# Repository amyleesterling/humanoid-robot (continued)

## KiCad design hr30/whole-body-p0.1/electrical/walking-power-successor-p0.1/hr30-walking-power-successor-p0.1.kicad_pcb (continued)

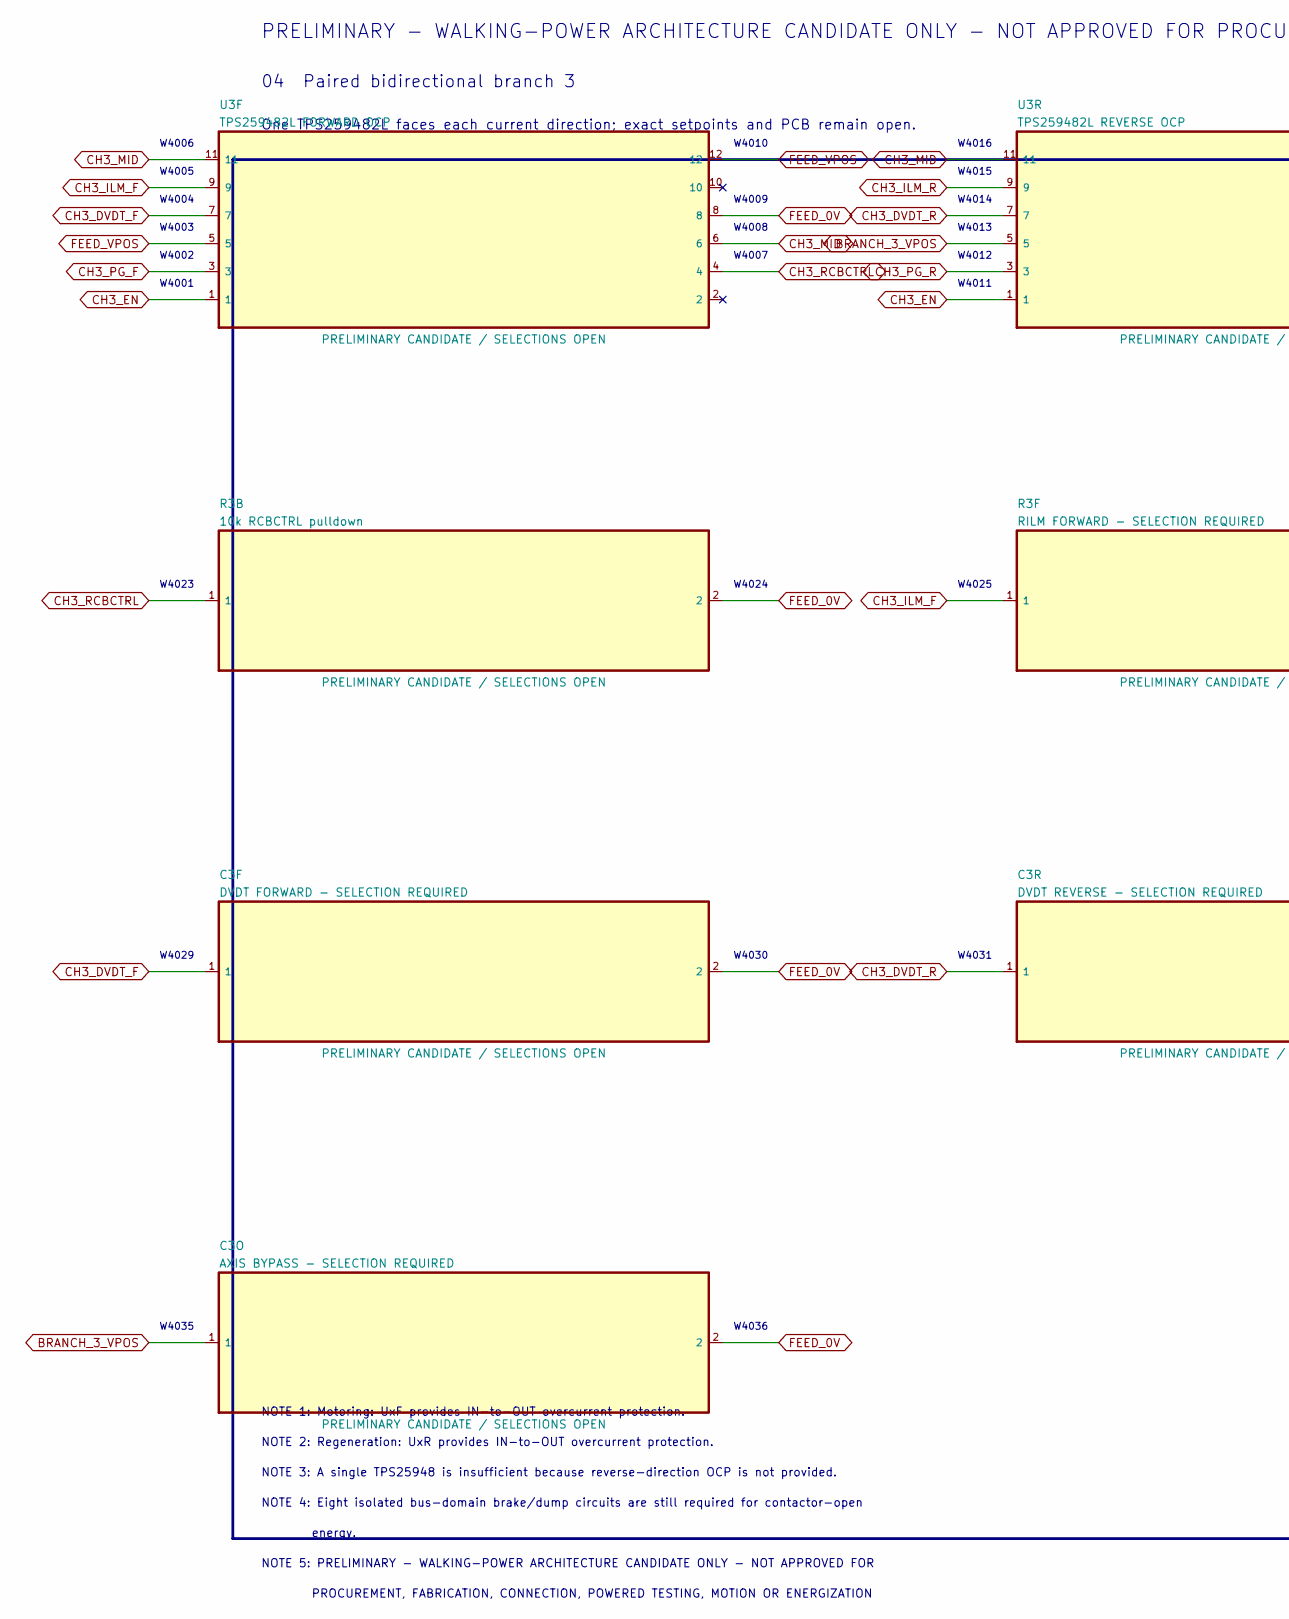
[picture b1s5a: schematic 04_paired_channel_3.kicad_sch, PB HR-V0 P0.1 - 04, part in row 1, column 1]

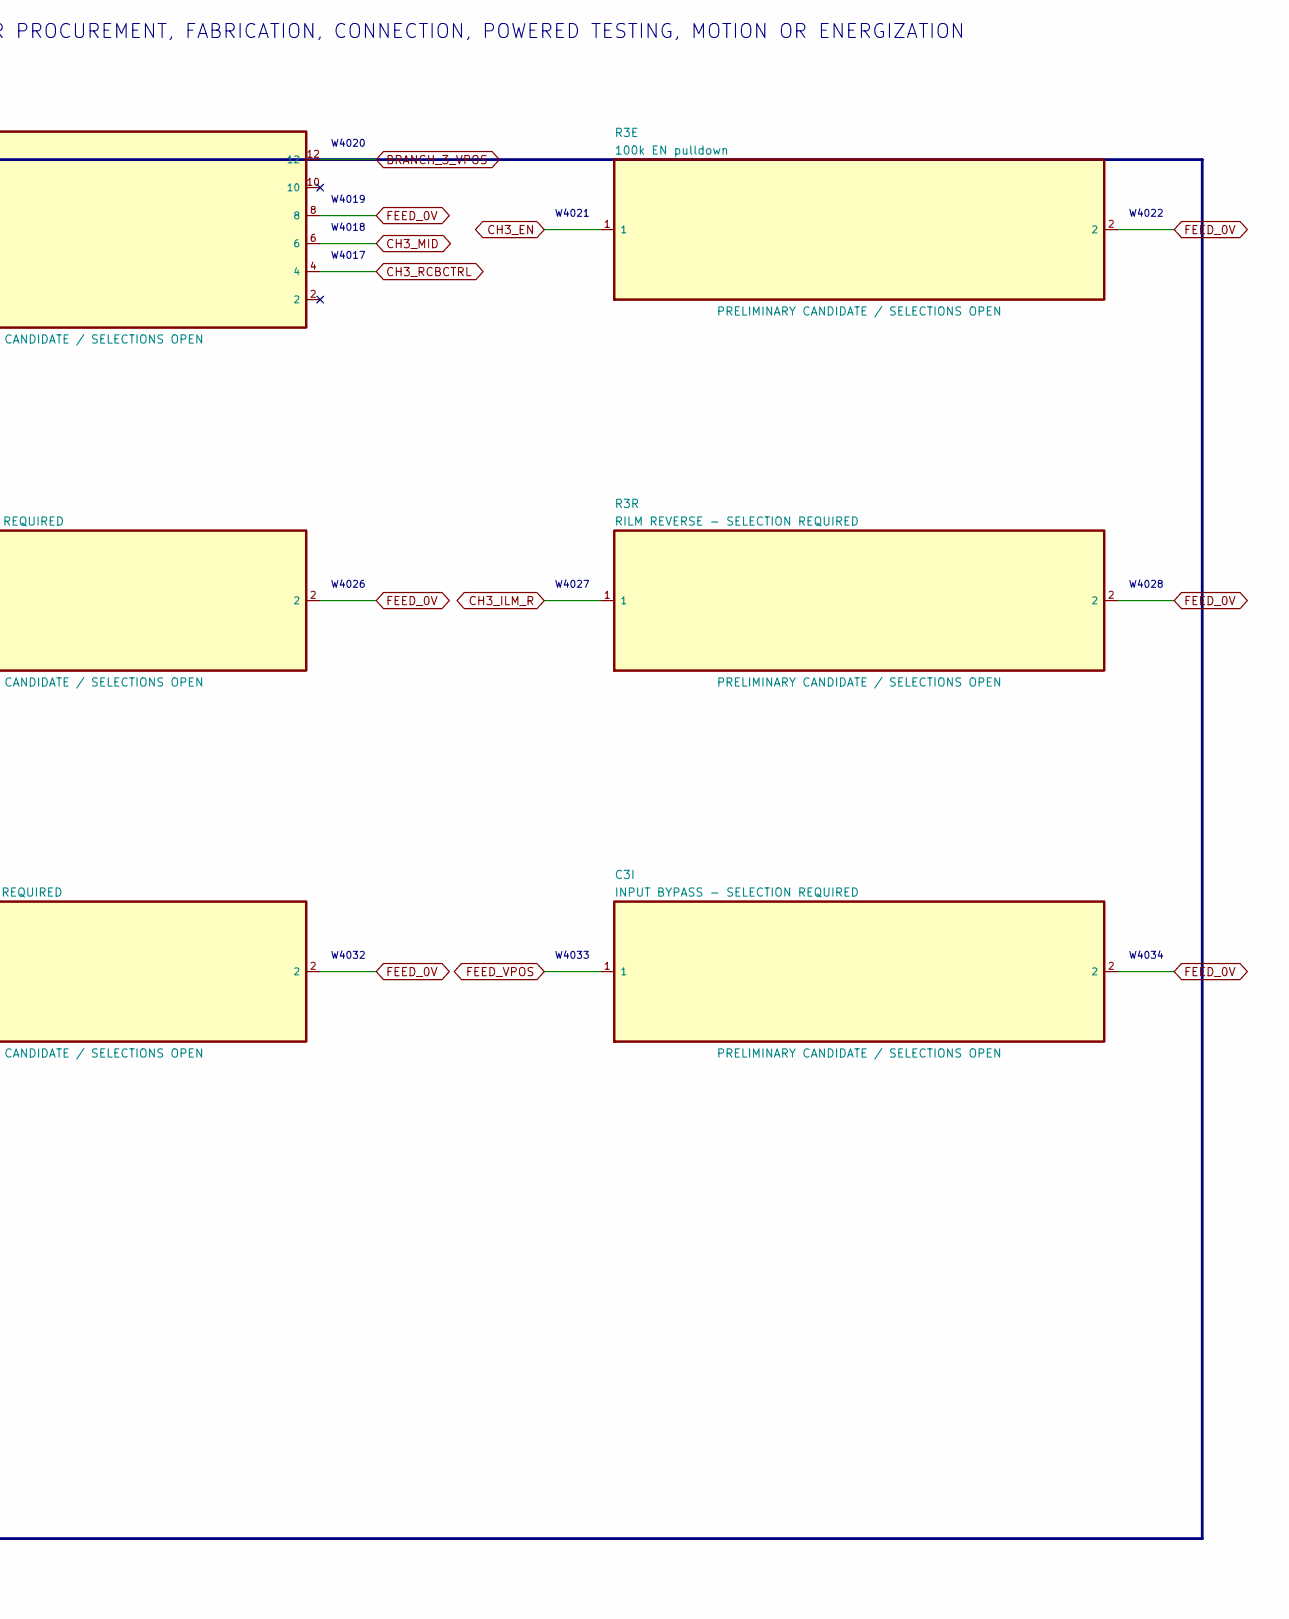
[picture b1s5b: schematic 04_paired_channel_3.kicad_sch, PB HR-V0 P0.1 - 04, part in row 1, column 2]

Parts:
C3F: DVDT FORWARD - SELECTION REQUIRED; C_0603_1608Metric
C3I: INPUT BYPASS - SELECTION REQUIRED; C_0805_2012Metric
C3O: AXIS BYPASS - SELECTION REQUIRED; C_0805_2012Metric
C3R: DVDT REVERSE - SELECTION REQUIRED; C_0603_1608Metric
R3B: 10k RCBCTRL pulldown; R_0603_1608Metric
R3E: 100k EN pulldown; R_0603_1608Metric
R3F: RILM FORWARD - SELECTION REQUIRED; R_0603_1608Metric
R3R: RILM REVERSE - SELECTION REQUIRED; R_0603_1608Metric
U3F: TPS259482L FORWARD OCP
U3R: TPS259482L REVERSE OCP

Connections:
BRANCH_3_VPOS: C3O.1, U3R.5, U3R.12; also elsewhere on the board
CH3_DVDT_F: C3F.1, U3F.7
CH3_DVDT_R: C3R.1, U3R.7
CH3_EN: R3E.1, U3F.1, U3R.1; also elsewhere on the board
CH3_ILM_F: R3F.1, U3F.9; also elsewhere on the board
CH3_ILM_R: R3R.1, U3R.9; also elsewhere on the board
CH3_ITIMER_F: U3F.10
CH3_ITIMER_R: U3R.10
CH3_MID: U3F.6, U3F.11, U3R.6, U3R.11
CH3_OV_F: U3F.2; also elsewhere on the board
CH3_OV_R: U3R.2; also elsewhere on the board
CH3_PG_F: U3F.3; also elsewhere on the board
CH3_PG_R: U3R.3; also elsewhere on the board
CH3_RCBCTRL: R3B.1, U3F.4, U3R.4; also elsewhere on the board
FEED_0V: C3F.2, C3I.2, C3O.2, C3R.2, R3B.2, R3E.2, R3F.2, R3R.2, U3F.8, U3R.8; also elsewhere on the board
FEED_VPOS: C3I.1, U3F.5, U3F.12; also elsewhere on the board

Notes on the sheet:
PRELIMINARY - WALKING-POWER ARCHITECTURE CANDIDATE ONLY - NOT APPROVED FOR PROCUREMENT, FABRICATION, CONNECTION, POWERED TESTING, MOTION OR ENERGIZATION
04 Paired bidirectional branch 3
One TPS259482L faces each current direction; exact setpoints and PCB remain open.
W4001
W4002
W4003
W4004
W4005
W4006
W4007
W4008
W4009
W4010
W4011
W4012
W4013
W4014
W4015
W4016
W4017
W4018
W4019
W4020
W4021
W4022
W4023
W4024
W4025
W4026
W4027
W4028
W4029
W4030
W4031
W4032
W4033
W4034
W4035
W4036
NOTE 1: Motoring: UxF provides IN-to-OUT overcurrent protection.

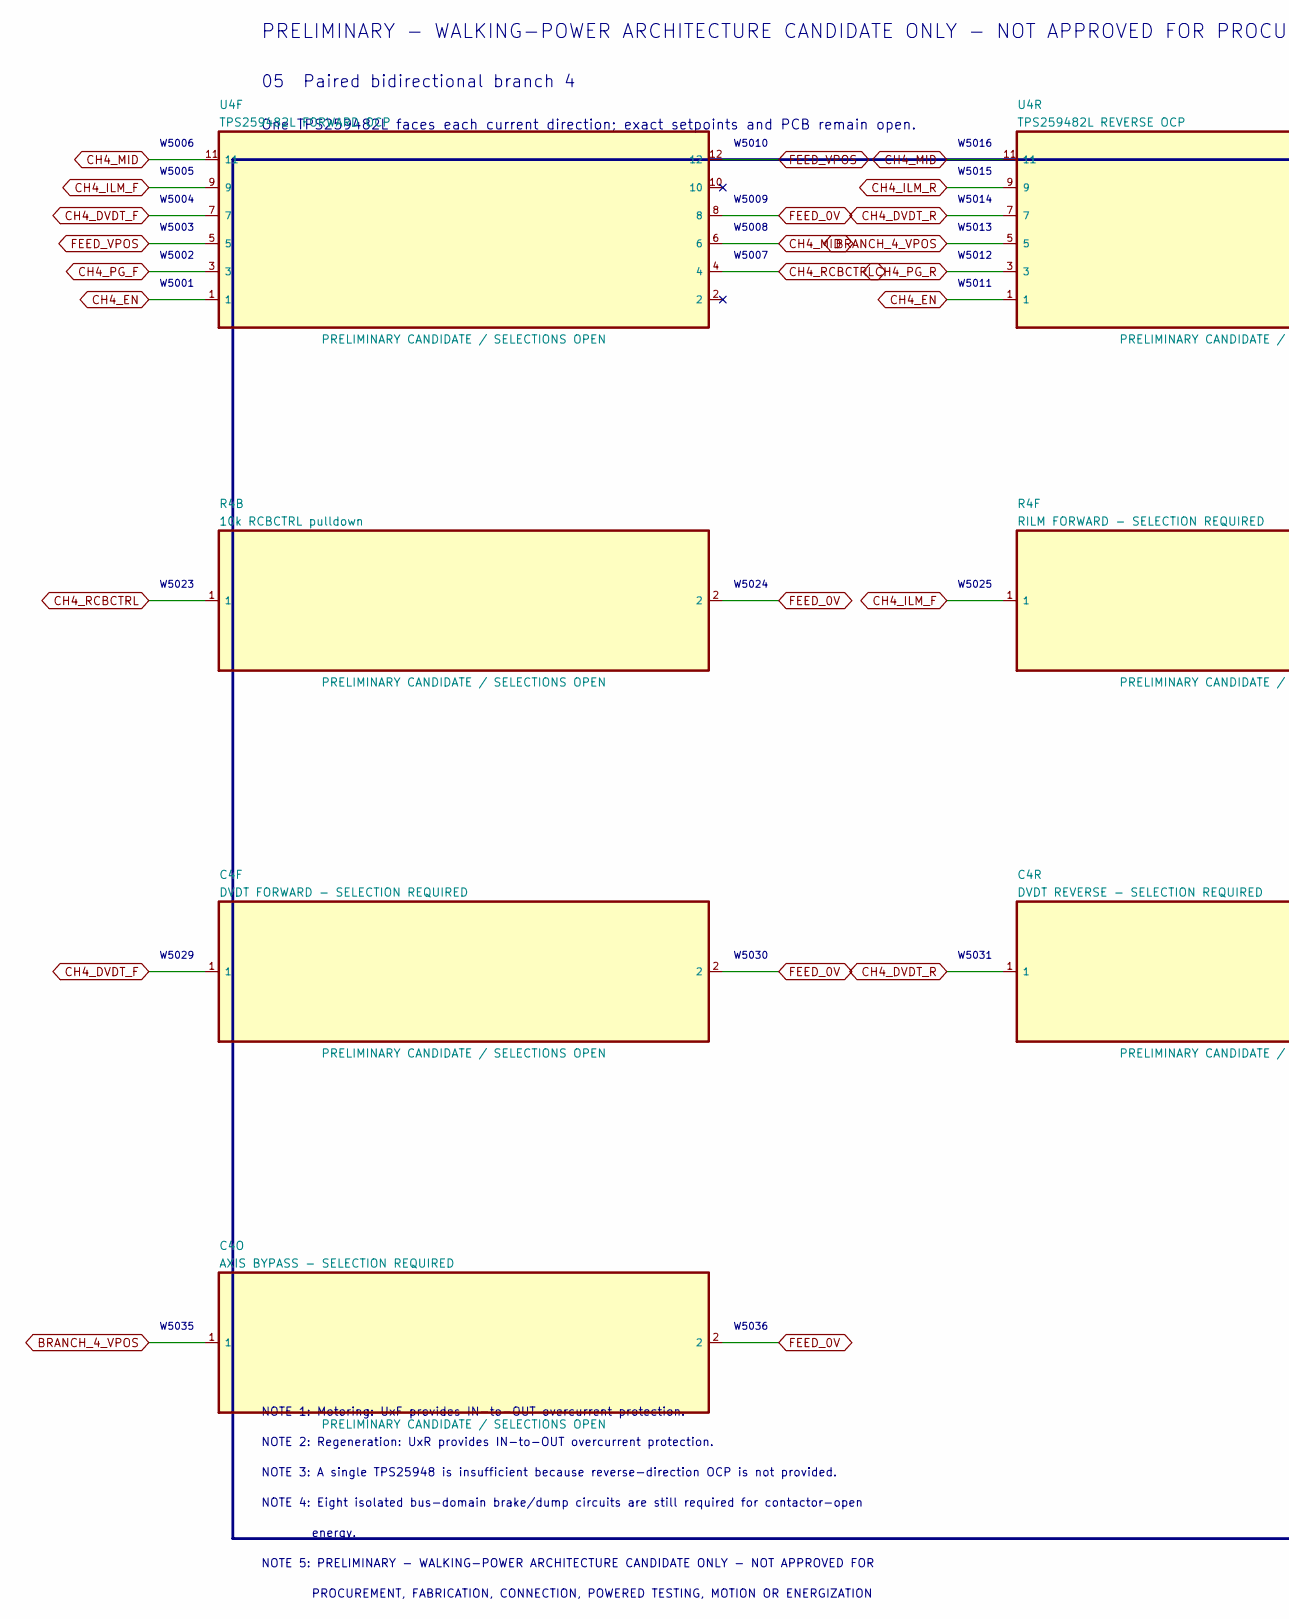
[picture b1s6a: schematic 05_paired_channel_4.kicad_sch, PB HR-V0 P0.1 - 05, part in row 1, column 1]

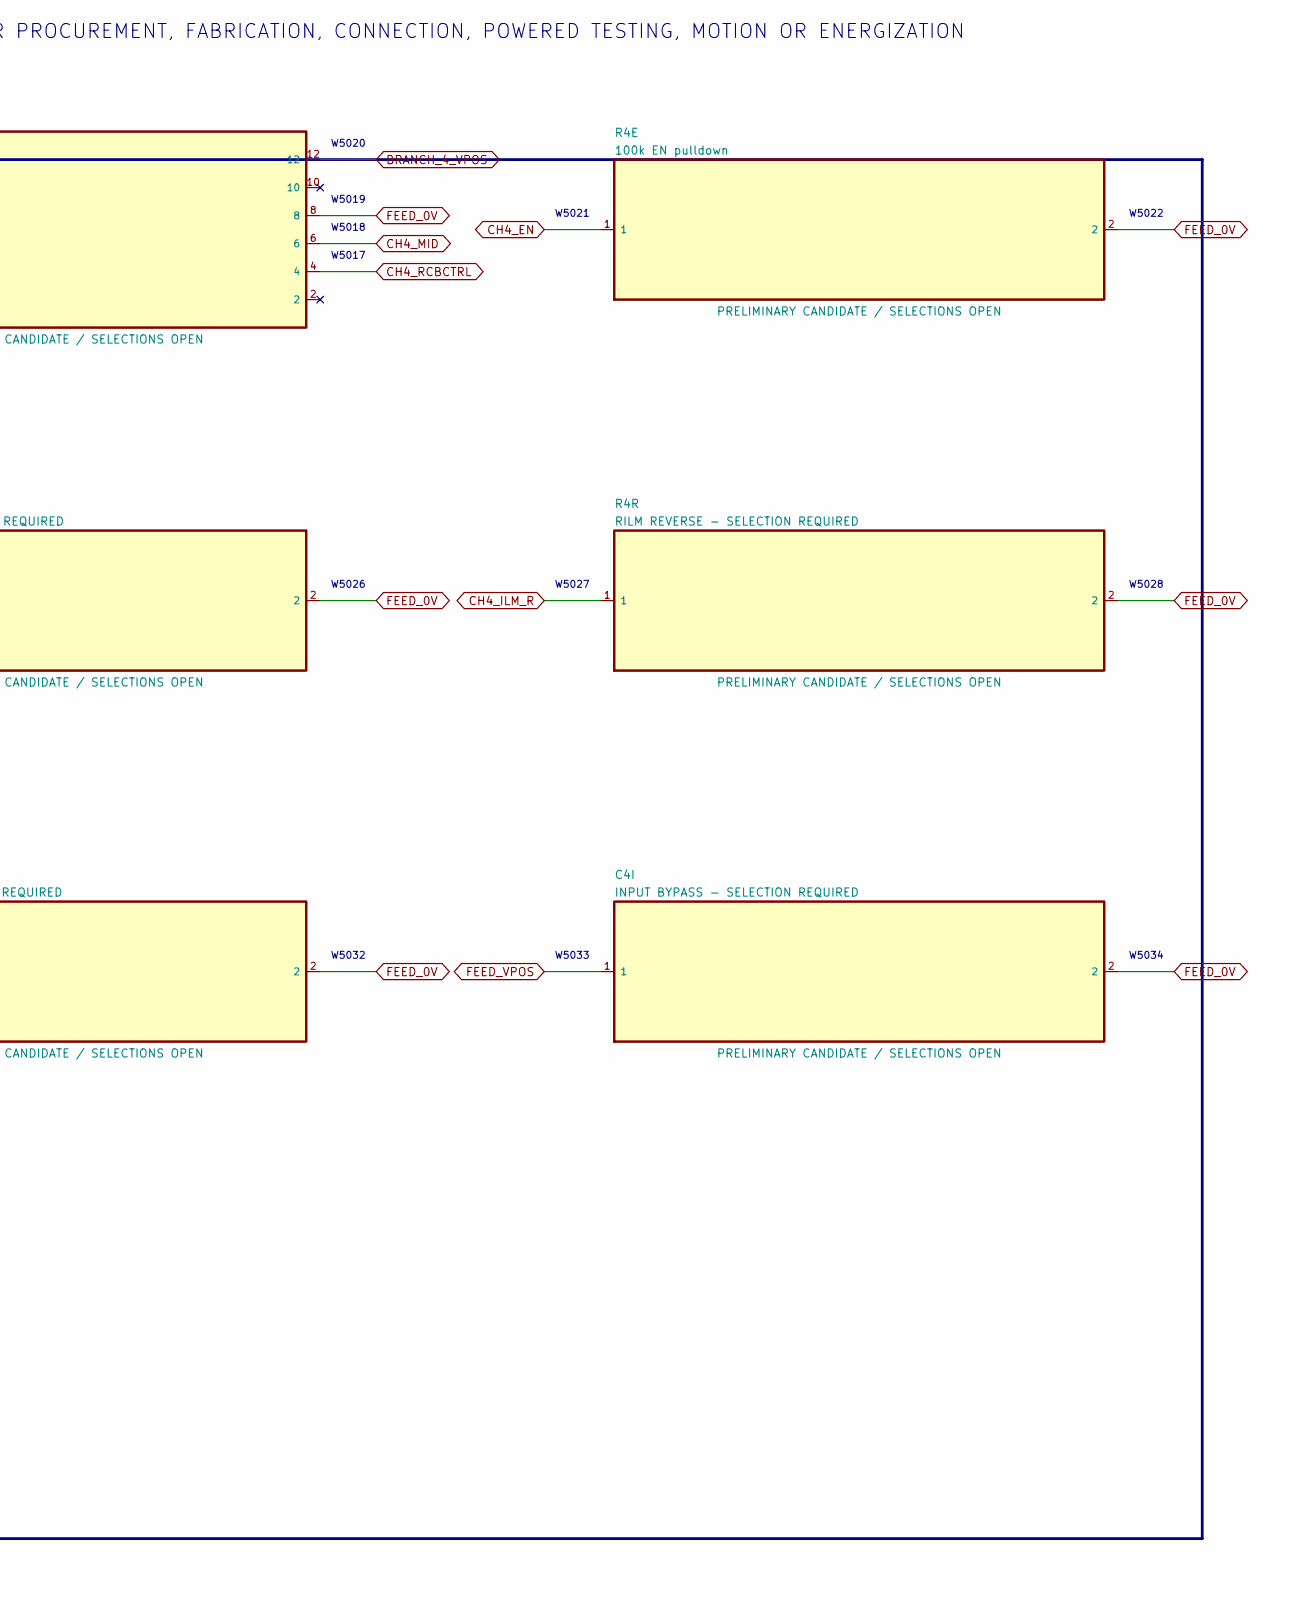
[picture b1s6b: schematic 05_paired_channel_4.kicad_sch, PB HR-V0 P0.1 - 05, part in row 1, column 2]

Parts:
C4F: DVDT FORWARD - SELECTION REQUIRED; C_0603_1608Metric
C4I: INPUT BYPASS - SELECTION REQUIRED; C_0805_2012Metric
C4O: AXIS BYPASS - SELECTION REQUIRED; C_0805_2012Metric
C4R: DVDT REVERSE - SELECTION REQUIRED; C_0603_1608Metric
R4B: 10k RCBCTRL pulldown; R_0603_1608Metric
R4E: 100k EN pulldown; R_0603_1608Metric
R4F: RILM FORWARD - SELECTION REQUIRED; R_0603_1608Metric
R4R: RILM REVERSE - SELECTION REQUIRED; R_0603_1608Metric
U4F: TPS259482L FORWARD OCP
U4R: TPS259482L REVERSE OCP

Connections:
BRANCH_4_VPOS: C4O.1, U4R.5, U4R.12; also elsewhere on the board
CH4_DVDT_F: C4F.1, U4F.7
CH4_DVDT_R: C4R.1, U4R.7
CH4_EN: R4E.1, U4F.1, U4R.1; also elsewhere on the board
CH4_ILM_F: R4F.1, U4F.9; also elsewhere on the board
CH4_ILM_R: R4R.1, U4R.9; also elsewhere on the board
CH4_ITIMER_F: U4F.10
CH4_ITIMER_R: U4R.10
CH4_MID: U4F.6, U4F.11, U4R.6, U4R.11
CH4_OV_F: U4F.2; also elsewhere on the board
CH4_OV_R: U4R.2; also elsewhere on the board
CH4_PG_F: U4F.3; also elsewhere on the board
CH4_PG_R: U4R.3; also elsewhere on the board
CH4_RCBCTRL: R4B.1, U4F.4, U4R.4; also elsewhere on the board
FEED_0V: C4F.2, C4I.2, C4O.2, C4R.2, R4B.2, R4E.2, R4F.2, R4R.2, U4F.8, U4R.8; also elsewhere on the board
FEED_VPOS: C4I.1, U4F.5, U4F.12; also elsewhere on the board

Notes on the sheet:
PRELIMINARY - WALKING-POWER ARCHITECTURE CANDIDATE ONLY - NOT APPROVED FOR PROCUREMENT, FABRICATION, CONNECTION, POWERED TESTING, MOTION OR ENERGIZATION
05 Paired bidirectional branch 4
One TPS259482L faces each current direction; exact setpoints and PCB remain open.
W5001
W5002
W5003
W5004
W5005
W5006
W5007
W5008
W5009
W5010
W5011
W5012
W5013
W5014
W5015
W5016
W5017
W5018
W5019
W5020
W5021
W5022
W5023
W5024
W5025
W5026
W5027
W5028
W5029
W5030
W5031
W5032
W5033
W5034
W5035
W5036
NOTE 1: Motoring: UxF provides IN-to-OUT overcurrent protection.

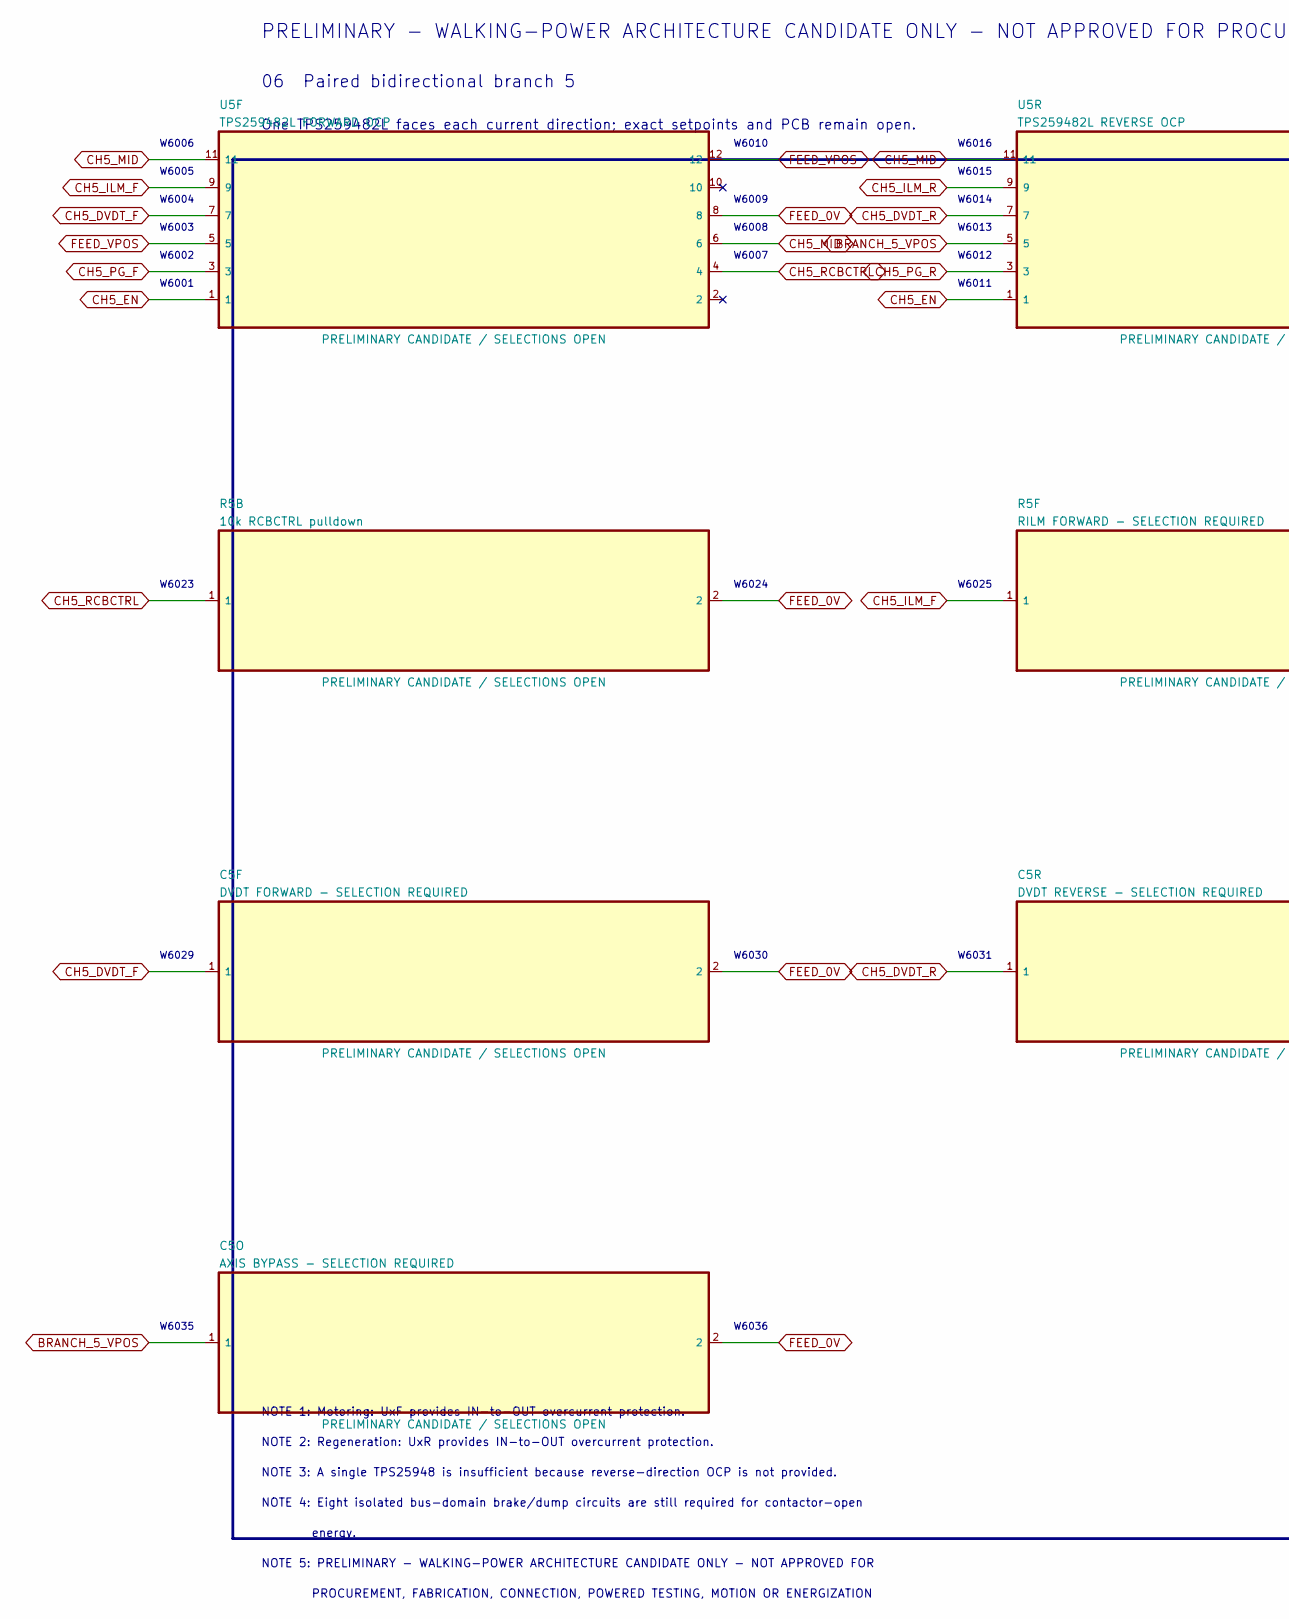
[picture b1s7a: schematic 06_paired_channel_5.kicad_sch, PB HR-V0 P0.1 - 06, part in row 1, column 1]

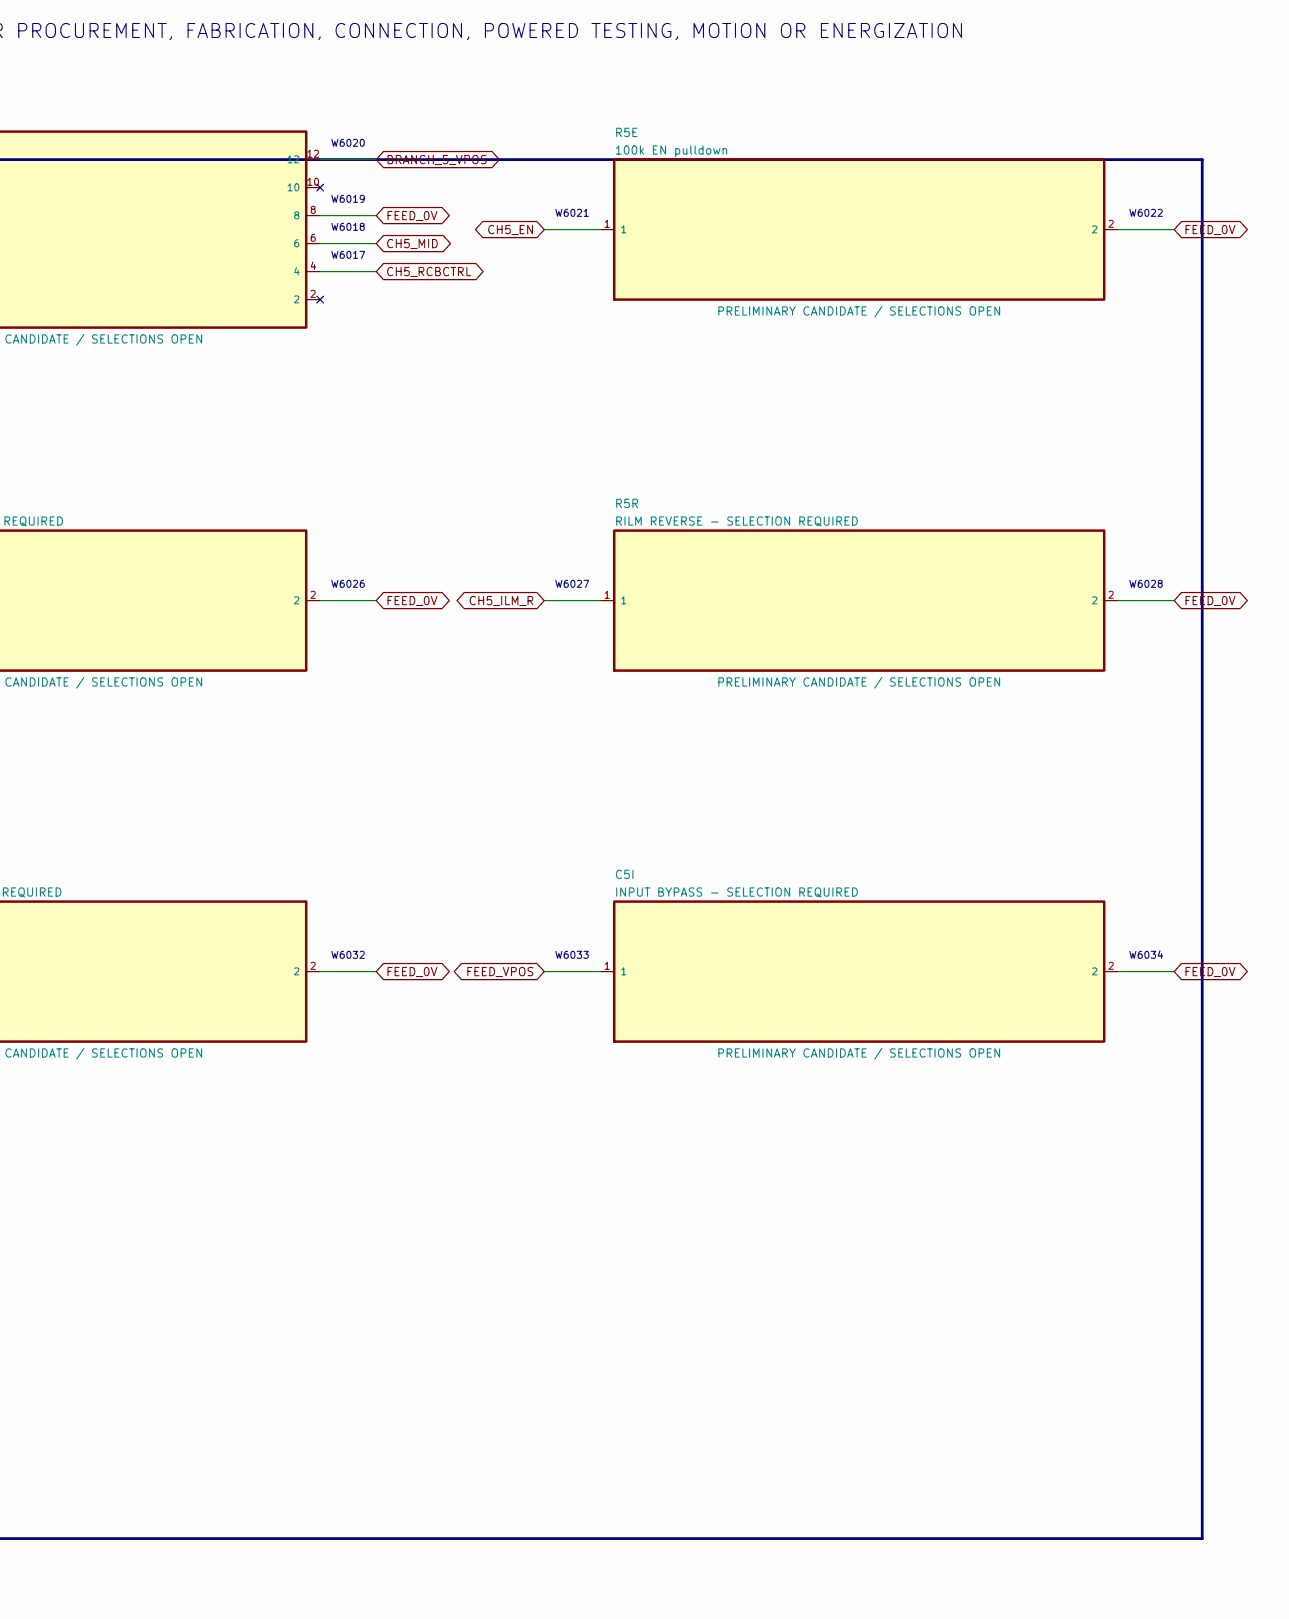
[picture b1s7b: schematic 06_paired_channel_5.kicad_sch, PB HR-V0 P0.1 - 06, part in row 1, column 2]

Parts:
C5F: DVDT FORWARD - SELECTION REQUIRED; C_0603_1608Metric
C5I: INPUT BYPASS - SELECTION REQUIRED; C_0805_2012Metric
C5O: AXIS BYPASS - SELECTION REQUIRED; C_0805_2012Metric
C5R: DVDT REVERSE - SELECTION REQUIRED; C_0603_1608Metric
R5B: 10k RCBCTRL pulldown; R_0603_1608Metric
R5E: 100k EN pulldown; R_0603_1608Metric
R5F: RILM FORWARD - SELECTION REQUIRED; R_0603_1608Metric
R5R: RILM REVERSE - SELECTION REQUIRED; R_0603_1608Metric
U5F: TPS259482L FORWARD OCP
U5R: TPS259482L REVERSE OCP

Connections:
BRANCH_5_VPOS: C5O.1, U5R.5, U5R.12; also elsewhere on the board
CH5_DVDT_F: C5F.1, U5F.7
CH5_DVDT_R: C5R.1, U5R.7
CH5_EN: R5E.1, U5F.1, U5R.1; also elsewhere on the board
CH5_ILM_F: R5F.1, U5F.9; also elsewhere on the board
CH5_ILM_R: R5R.1, U5R.9; also elsewhere on the board
CH5_ITIMER_F: U5F.10
CH5_ITIMER_R: U5R.10
CH5_MID: U5F.6, U5F.11, U5R.6, U5R.11
CH5_OV_F: U5F.2; also elsewhere on the board
CH5_OV_R: U5R.2; also elsewhere on the board
CH5_PG_F: U5F.3; also elsewhere on the board
CH5_PG_R: U5R.3; also elsewhere on the board
CH5_RCBCTRL: R5B.1, U5F.4, U5R.4; also elsewhere on the board
FEED_0V: C5F.2, C5I.2, C5O.2, C5R.2, R5B.2, R5E.2, R5F.2, R5R.2, U5F.8, U5R.8; also elsewhere on the board
FEED_VPOS: C5I.1, U5F.5, U5F.12; also elsewhere on the board

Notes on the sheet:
PRELIMINARY - WALKING-POWER ARCHITECTURE CANDIDATE ONLY - NOT APPROVED FOR PROCUREMENT, FABRICATION, CONNECTION, POWERED TESTING, MOTION OR ENERGIZATION
06 Paired bidirectional branch 5
One TPS259482L faces each current direction; exact setpoints and PCB remain open.
W6001
W6002
W6003
W6004
W6005
W6006
W6007
W6008
W6009
W6010
W6011
W6012
W6013
W6014
W6015
W6016
W6017
W6018
W6019
W6020
W6021
W6022
W6023
W6024
W6025
W6026
W6027
W6028
W6029
W6030
W6031
W6032
W6033
W6034
W6035
W6036
NOTE 1: Motoring: UxF provides IN-to-OUT overcurrent protection.

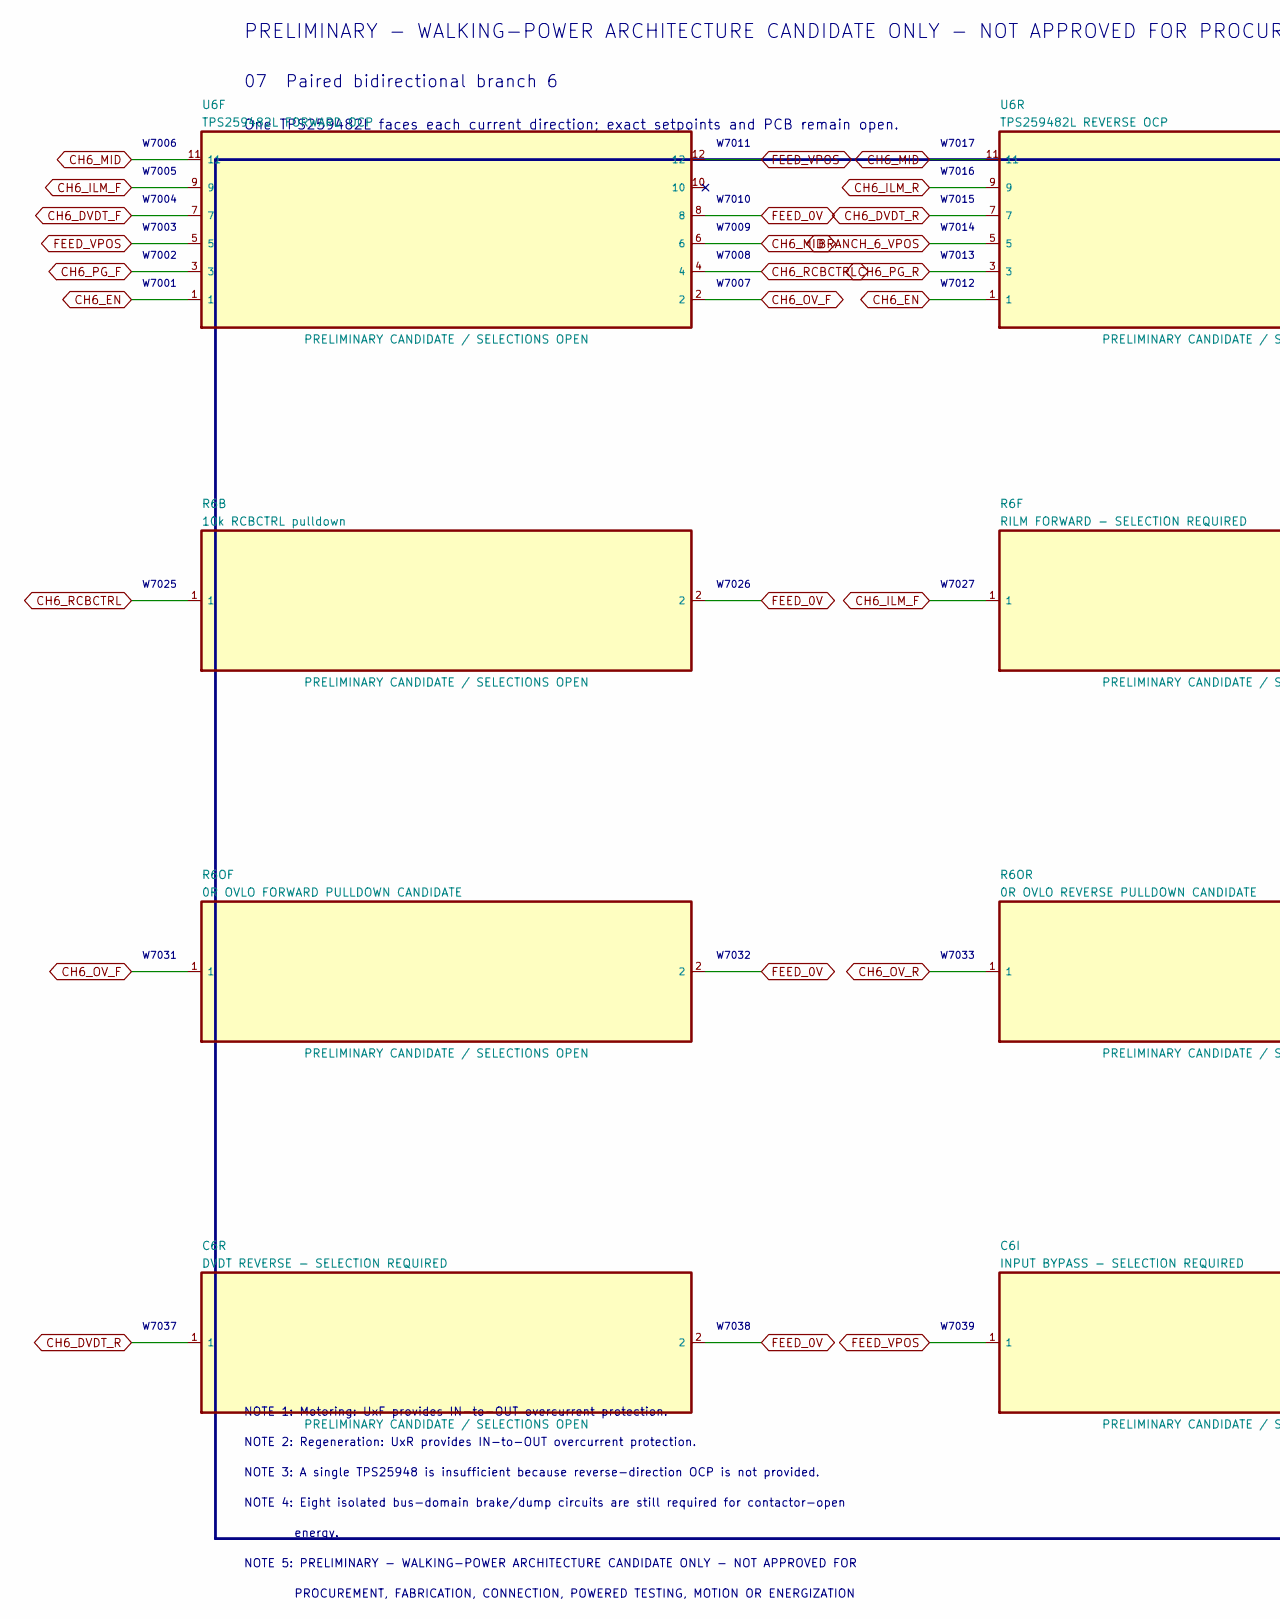
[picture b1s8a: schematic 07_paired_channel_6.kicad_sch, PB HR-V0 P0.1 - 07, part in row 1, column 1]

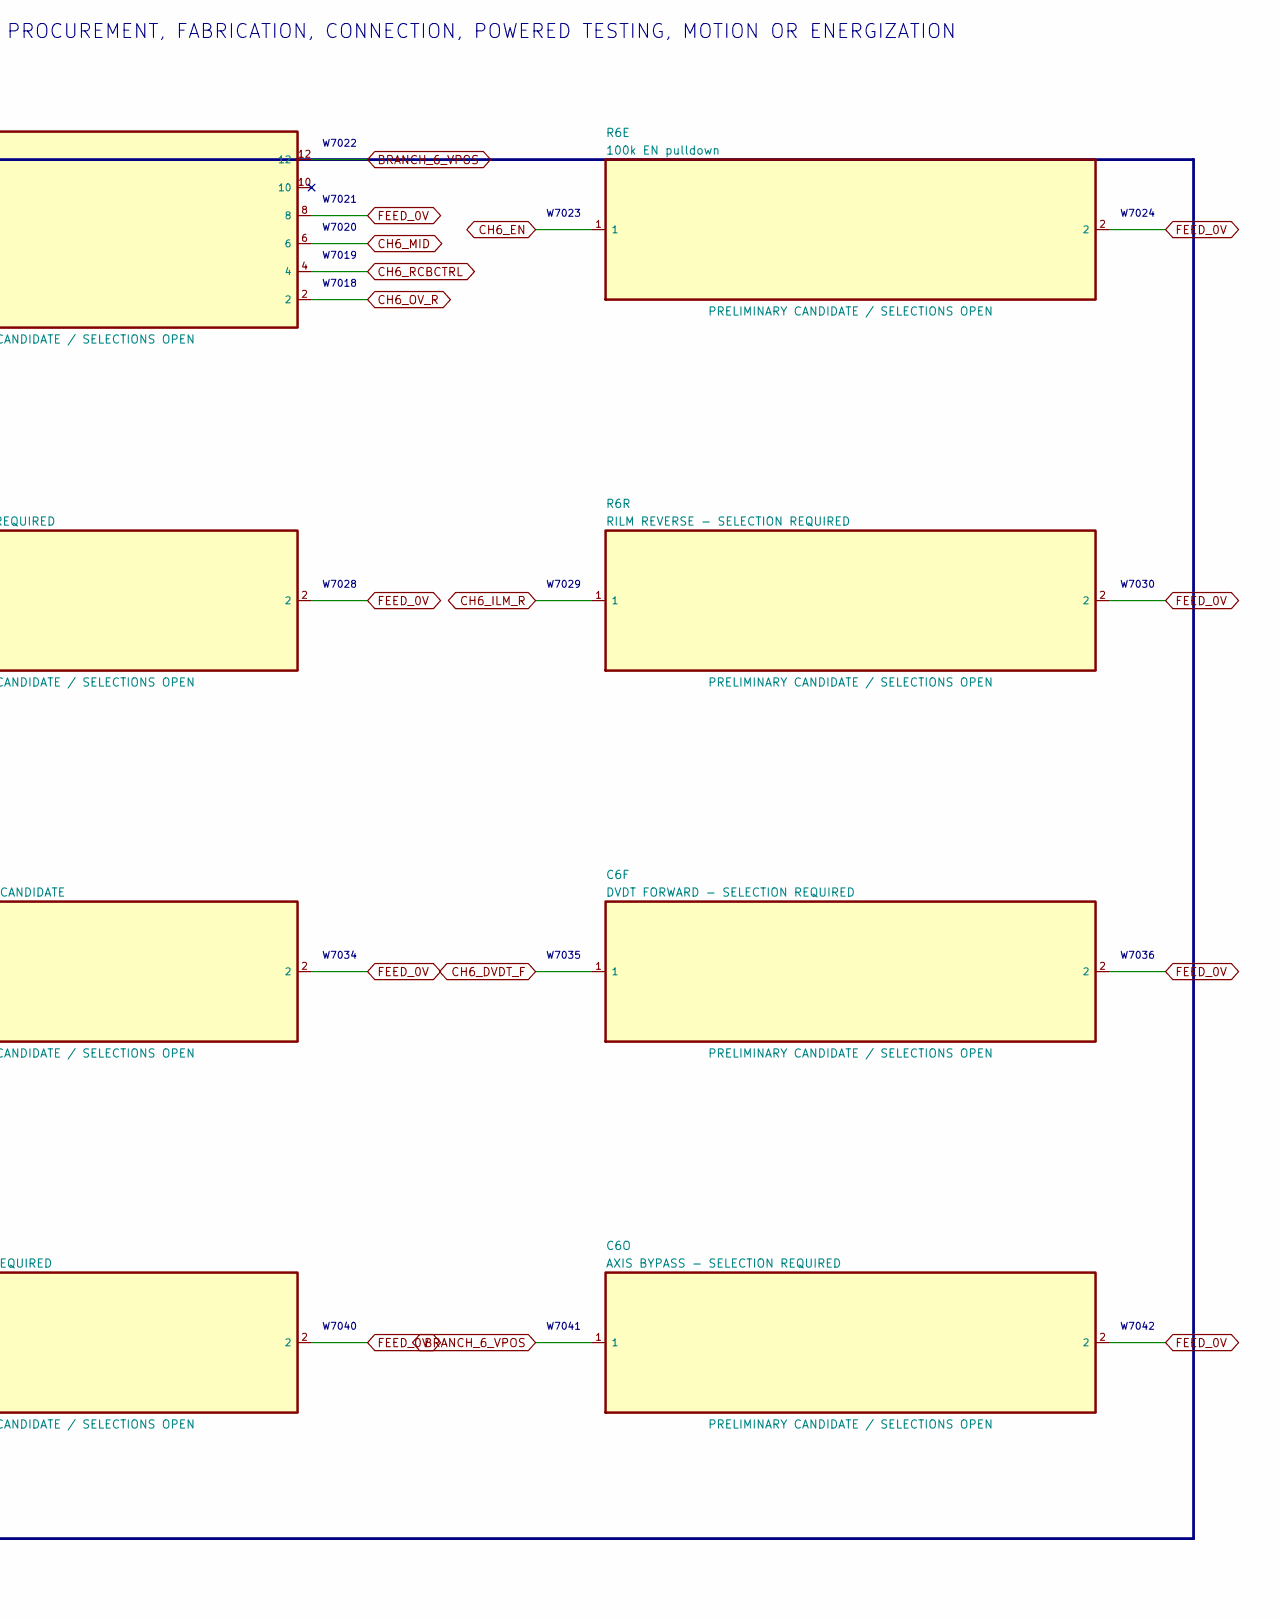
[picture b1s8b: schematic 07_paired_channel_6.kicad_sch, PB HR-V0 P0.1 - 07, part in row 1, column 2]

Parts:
C6F: DVDT FORWARD - SELECTION REQUIRED; C_0603_1608Metric
C6I: INPUT BYPASS - SELECTION REQUIRED; C_0805_2012Metric
C6O: AXIS BYPASS - SELECTION REQUIRED; C_0805_2012Metric
C6R: DVDT REVERSE - SELECTION REQUIRED; C_0603_1608Metric
R6B: 10k RCBCTRL pulldown; R_0603_1608Metric
R6E: 100k EN pulldown; R_0603_1608Metric
R6F: RILM FORWARD - SELECTION REQUIRED; R_0603_1608Metric
R6OF: 0R OVLO FORWARD PULLDOWN CANDIDATE; R_0603_1608Metric
R6OR: 0R OVLO REVERSE PULLDOWN CANDIDATE; R_0603_1608Metric
R6R: RILM REVERSE - SELECTION REQUIRED; R_0603_1608Metric
U6F: TPS259482L FORWARD OCP; TI_YWP0012A_PowerWCSP_2.441x1.728mm
U6R: TPS259482L REVERSE OCP; TI_YWP0012A_PowerWCSP_2.441x1.728mm

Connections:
BRANCH_6_VPOS: C6O.1, U6R.5, U6R.12; also elsewhere on the board
CH6_DVDT_F: C6F.1, U6F.7
CH6_DVDT_R: C6R.1, U6R.7
CH6_EN: R6E.1, U6F.1, U6R.1; also elsewhere on the board
CH6_ILM_F: R6F.1, U6F.9; also elsewhere on the board
CH6_ILM_R: R6R.1, U6R.9; also elsewhere on the board
CH6_ITIMER_F: U6F.10
CH6_ITIMER_R: U6R.10
CH6_MID: U6F.6, U6F.11, U6R.6, U6R.11
CH6_OV_F: R6OF.1, U6F.2
CH6_OV_R: R6OR.1, U6R.2
CH6_PG_F: U6F.3; also elsewhere on the board
CH6_PG_R: U6R.3; also elsewhere on the board
CH6_RCBCTRL: R6B.1, U6F.4, U6R.4; also elsewhere on the board
FEED_0V: C6F.2, C6I.2, C6O.2, C6R.2, R6B.2, R6E.2, R6F.2, R6OF.2, R6OR.2, R6R.2, U6F.8, U6R.8; also elsewhere on the board
FEED_VPOS: C6I.1, U6F.5, U6F.12; also elsewhere on the board

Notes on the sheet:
PRELIMINARY - WALKING-POWER ARCHITECTURE CANDIDATE ONLY - NOT APPROVED FOR PROCUREMENT, FABRICATION, CONNECTION, POWERED TESTING, MOTION OR ENERGIZATION
07 Paired bidirectional branch 6
One TPS259482L faces each current direction; exact setpoints and PCB remain open.
W7001
W7002
W7003
W7004
W7005
W7006
W7007
W7008
W7009
W7010
W7011
W7012
W7013
W7014
W7015
W7016
W7017
W7018
W7019
W7020
W7021
W7022
W7023
W7024
W7025
W7026
W7027
W7028
W7029
W7030
W7031
W7032
W7033
W7034
W7035
W7036
W7037

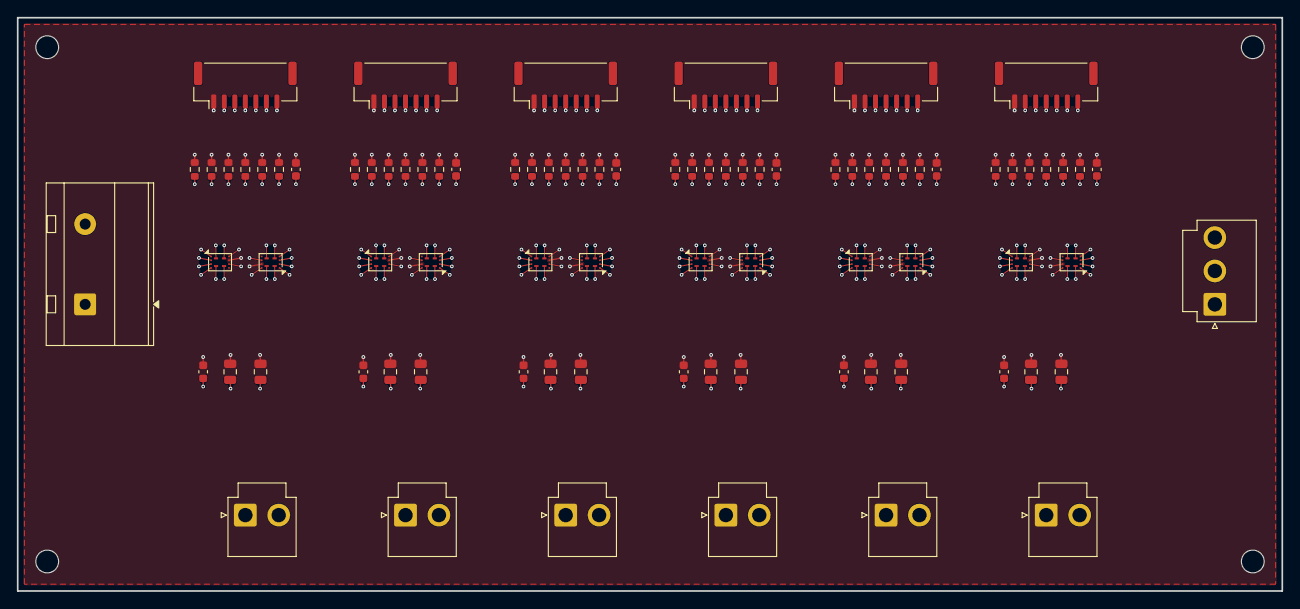
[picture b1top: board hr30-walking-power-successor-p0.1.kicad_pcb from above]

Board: 10 copper layers, 150.0 x 68.0 mm, 90 parts (0 on the bottom side), 74 nets.

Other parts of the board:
MH1, MH2, MH3, MH4: M2.5 BOARD-ONLY; MountingHole_2.7mm_M2.5
R1OF, R3OF, R4OF, R5OF: 0R OVLO FORWARD PULLDOWN CANDIDATE; R_0603_1608Metric
R1OR, R3OR, R4OR, R5OR: 0R OVLO REVERSE PULLDOWN CANDIDATE; R_0603_1608Metric

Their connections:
CH1_OV_F: R1OF.1; also elsewhere on the board
CH1_OV_R: R1OR.1; also elsewhere on the board
CH3_OV_F: R3OF.1; also elsewhere on the board
CH3_OV_R: R3OR.1; also elsewhere on the board
CH4_OV_F: R4OF.1; also elsewhere on the board
CH4_OV_R: R4OR.1; also elsewhere on the board
CH5_OV_F: R5OF.1; also elsewhere on the board
CH5_OV_R: R5OR.1; also elsewhere on the board
FEED_0V: R1OF.2, R1OR.2, R3OF.2, R3OR.2, R4OF.2, R4OR.2, R5OF.2, R5OR.2; also elsewhere on the board
